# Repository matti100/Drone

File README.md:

# Autonomous Quadrotor Project

A multidisciplinary quadrotor project developed to study and implement the main engineering aspects of a small unmanned aerial vehicle, combining **flight dynamics, simulation, guidance and control, state estimation, electronics, embedded systems, hardware testing and IoT-based control**.

The project combines a MATLAB/Simulink simulation environment with the supporting embedded software, electronics, documentation, testing activities and web interface required for a complete quadrotor system.

---

## Overview

The project was developed to apply aerospace engineering concepts to a real-world autonomous flight system.

The main areas investigated throughout the project are:

* 6-DOF quadrotor flight dynamics
* Nonlinear system modeling
* Linearization and system analysis
* PID control
* Linear Quadratic Regulator (LQR)
* Nonlinear Model Predictive Control (NMPC)
* Kalman-filter-based state estimation
* Sensor fusion
* Trajectory tracking
* Controller tuning
* Embedded systems and Arduino
* Electronics and PCB design
* Hardware testing
* IoT-based drone control

The repository is organized into separate directories according to the different aspects of the project, from theoretical modeling and simulation to embedded implementation and system testing.

---

# Repository Structure

```text
Drone/
│
├── simulator/
│   ├── MATLAB and Simulink simulation files
│   └── Flight dynamics, control and state-estimation models
│
├── arduino_sketches/
│   ├── Main Arduino code
│   ├── Supporting functions
│   └── Required libraries and modules
│
├── electronics/
│   ├── Electrical schematics
│   └── PCB designs
│
├── docs/
│   ├── Project documentation
│   └── Component datasheets
│
├── testing/
│   └── Hardware and system testing
│
├── WebApp/
│   └── drone-web-app/
│       └── Web application for IoT-based drone control
│
└── README.md
```

Each directory addresses a different part of the overall system.

---

# Simulator

The `simulator/` directory contains the **MATLAB and Simulink simulation environment** developed to model, analyze and control the quadrotor before its physical implementation.

The simulator provides a model-based environment in which the vehicle dynamics, control algorithms, state-estimation techniques and trajectory-tracking performance can be developed and evaluated independently of the physical hardware.

The main components investigated within the simulator are:

* Nonlinear quadrotor dynamics
* Linearized hover model
* Stability and controllability analysis
* PID control
* LQR control
* Nonlinear Model Predictive Control
* Kalman-filter-based state estimation
* Controller tuning
* Closed-loop trajectory tracking
* Simulation visualization and animation

---

## Running the Simulator

The main entry point for the simulation is `simulator.m`, located in the `simulator/` directory.

Before running the simulation, open `simulator.m` and configure the vehicle parameters, initial conditions, desired state, simulation settings, controller, state estimator and visualization options.

Once the parameters have been configured, run:

```matlab
simulator
```

The simulation initializes the quadrotor model, executes the selected control and estimation architecture and generates the requested plots and animation.

---

### 1. Vehicle Parameters

The physical parameters of the quadrotor can be modified at the beginning of `simulator.m`.

```matlab
params.m = 0.8;                 % [kg] Mass

params.Ix = 15.67e-3;           % [kg m^2] Moment of inertia about X
params.Iy = 15.67e-3;           % [kg m^2] Moment of inertia about Y
params.Iz = 28.34e-3;           % [kg m^2] Moment of inertia about Z

params.armLength = 0.3;         % [m] Arm length
params.bodySize = 0.2;          % [m] Body size
params.rotRad = 0.1;             % [m] Rotor radius

params.k_f = 1.4e-5 / 9.54929658;  % Lift coefficient
params.k_m = 1.78e-6 / 9.54929658; % Torque coefficient

params.g = 9.81;                % [m/s^2] Gravitational acceleration
```

These parameters define the physical model used by the simulator.

The parameters that can be modified include:

| Parameter          | Description                               | Unit  |
| ------------------ | ----------------------------------------- | ----- |
| `params.m`         | Vehicle mass                              | kg    |
| `params.Ix`        | Principal moment of inertia about X       | kg·m² |
| `params.Iy`        | Principal moment of inertia about Y       | kg·m² |
| `params.Iz`        | Principal moment of inertia about Z       | kg·m² |
| `params.armLength` | Distance from the center to the rotor arm | m     |
| `params.bodySize`  | Approximate body size                     | m     |
| `params.rotRad`    | Rotor radius                              | m     |
| `params.k_f`       | Rotor lift coefficient                    | —     |
| `params.k_m`       | Rotor torque coefficient                  | —     |
| `params.g`         | Gravitational acceleration                | m/s²  |

The inertia matrix is then constructed as:

```matlab
params.I = diag([params.Ix, params.Iy, params.Iz]);
```

---

### 2. Numerical Integration

The simulation integration step is controlled by:

```matlab
params.dt = 0.001;       % [s]
```

The current implementation uses **explicit Euler integration** to propagate the nonlinear equations of motion.

Therefore, `params.dt` controls the numerical integration step and directly affects both the simulation resolution and computational cost.

A smaller value generally provides a finer temporal resolution at the expense of increased computational cost.

---

### 3. Initial Conditions

The initial state of the quadrotor is defined through the 12-state vector:

```matlab
x0 = zeros(12,1);
```

The state follows the convention:

```text
x0 = [x y z vx vy vz phi theta psi p q r]ᵀ
```

Individual initial conditions can be modified directly:

```matlab
x0(1) = 0;       % Initial x position [m]
x0(2) = 0;       % Initial y position [m]
x0(3) = 0;       % Initial z position [m]

x0(4) = 0;       % Initial x velocity [m/s]
x0(5) = 0;       % Initial y velocity [m/s]
x0(6) = 0;       % Initial z velocity [m/s]

x0(7) = 0.3;     % Initial roll [rad]
x0(8) = 0.5;     % Initial pitch [rad]
x0(9) = 0;       % Initial yaw [rad]

x0(10) = 0;      % Initial roll rate [rad/s]
x0(11) = 0;      % Initial pitch rate [rad/s]
x0(12) = 0;      % Initial yaw rate [rad/s]
```

This allows the user to investigate different initial flight conditions and attitude perturbations.

---

### 4. Desired State

The target position and attitude are defined through the `desideredState` structure:

```matlab
desideredState = struct();

desideredState.rDes = [-0.5, 1, 1]';    % [m]
desideredState.attDes = [0, 0, 0]';     % [rad]
```

The desired state consists of:

* Desired position: `rDes = [x, y, z]`
* Desired attitude: `attDes = [phi, theta, psi]`

For example, to command the quadrotor to a different position:

```matlab
desideredState.rDes = [1, 2, 1.5]';
```

The desired yaw angle can also be modified:

```matlab
desideredState.attDes = [0, 0, pi/2]';
```

---

### 5. Simulation Time

The simulation interval is defined using:

```matlab
t0 = 0;          % [s]
tmax = 10;       % [s]

tspan = [t0, tmax];
```

Modify `tmax` to change the total simulation duration.

For example:

```matlab
tmax = 20;
```

runs the simulation for 20 seconds.

---

### 6. Control Mode

The controller is selected using the `control` flag:

```matlab
control = 2;
```

The available modes are:

| Value | Configuration            |
| ----: | ------------------------ |
|  `-1` | PID + linear dynamics    |
|   `0` | PID + nonlinear dynamics |
|   `1` | LQR + linear dynamics    |
|   `2` | LQR + nonlinear dynamics |
|   `3` | Nonlinear MPC            |

For example:

```matlab
control = 0;
```

runs the PID controller using the nonlinear quadrotor dynamics.

To evaluate the LQR controller on the nonlinear plant:

```matlab
control = 2;
```

To use nonlinear MPC:

```matlab
control = 3;
```

The different configurations allow the effect of model linearization and nonlinear dynamics on closed-loop performance to be investigated.

---

### 7. State Estimation

The state-estimation architecture is selected using:

```matlab
estimation = 0;
```

The available options are:

| Value | Configuration       |
| ----: | ------------------- |
|   `0` | No state estimation |
|   `1` | Kalman filter       |

When `estimation = 0`, the controller receives the simulated state directly.

When `estimation = 1`, simulated accelerometer and gyroscope measurements are generated with noise and processed by the Kalman filter before being provided to the control architecture.

For example:

```matlab
estimation = 1;
```

enables the Kalman-filter-based state estimator.

---

### 8. Discrete-Time Sampling

The controller and estimator sampling time is controlled by:

```matlab
sampleTime = 0.005;       % [s]
```

The integration step `params.dt` and the controller/estimator sampling time are independent.

This allows the simulator to represent a system where the continuous-time dynamics are integrated at a finer resolution than the controller and estimator update rate.

Setting:

```matlab
sampleTime = params.dt;
```

makes the controller and estimator update at every integration step.

---

### 9. Visualization

Two flags control the graphical output:

```matlab
plot_flag = 1;
anim_flag = 1;
```

Set:

```matlab
plot_flag = 1;
```

to generate the simulation plots or:

```matlab
plot_flag = 0;
```

to disable plotting.

The animation can similarly be enabled or disabled using:

```matlab
anim_flag = 1;
```

or:

```matlab
anim_flag = 0;
```

When enabled, the simulator generates 2D views of the XY, YZ and XZ planes as well as a 3D visualization of the quadrotor trajectory.

---

### 10. PID Gain Tuning

When using PID control, the controller gains can be manually specified through the `kP`, `kI` and `kD` vectors.

The six controlled quantities correspond to:

```text
1. Altitude
2. Desired roll
3. Desired pitch
4. Roll
5. Pitch
6. Yaw
```

For example:

```matlab
kP = [20;
      -0.4;
       0.4;
       1;
       1;
       1.2];

kI = [10;
      -0.09;
       0.09;
       0.13;
       0.13;
       0.03];

kD = [10;
      -0.25;
       0.25;
       0.66;
       0.66;
       0.9];
```

These values are passed to `gainBuilder()` and then used by the PID controllers.

---

### 11. Automatic PID Tuning

The simulator also provides two automated PID tuning methods through the `tuner_flag`.

```matlab
tuner_flag = 0;
```

The available options are:

| Value | Tuning method       |
| ----: | ------------------- |
|   `0` | No automatic tuning |
|   `1` | Gradient Descent    |
|   `2` | Genetic Algorithm   |

#### Gradient Descent

```matlab
tuner_flag = 1;
```

The current implementation uses:

```matlab
maxIter = 10000;
tol = 1e-6;
alpha = 10;
```

The initial PID gains are randomly generated and then optimized using the PID tuning routine.

The resulting gains are saved to:

```text
tunedGains_gradient.mat
```

#### Genetic Algorithm

```matlab
tuner_flag = 2;
```

The current implementation uses:

```matlab
pop_size = 100;
maxGen = 2000;
tol = 1;
mutation_rate = 0.6;
kMax = 10;
```

The optimized gains are saved to:

```text
tunedGains_ga.mat
```

When automatic tuning is enabled, plotting is automatically disabled during the optimization process to avoid generating unnecessary graphical output.

---

### 12. Nonlinear MPC Parameters

When:

```matlab
control = 3;
```

the nonlinear MPC controller is used.

The main MPC parameters are defined inside the `MPC()` method in `Drone3.m`.

The prediction horizon is:

```matlab
N = 25;
```

and the MPC prediction time step is:

```matlab
dT = 0.1;
```

The control inputs are constrained by:

```text
0 ≤ u₁ ≤ 100
-100 ≤ u₂ ≤ 100
-100 ≤ u₃ ≤ 100
-100 ≤ u₄ ≤ 100
```

The MPC cost function uses weighting matrices for state-tracking error and control effort:

```matlab
Q = eye(6)*10;
Q(3,3) = 100;
Q(6,6) = 50;

R = eye(4)*5;
```

The optimization problem is solved using MATLAB's `fmincon` with the interior-point algorithm.

---

### 13. Running a Basic Simulation

A simple way to run the simulator is to use the default configuration:

```matlab
control = 2;       % LQR + nonlinear dynamics
estimation = 0;    % No state estimation

plot_flag = 1;
anim_flag = 1;

tuner_flag = 0;
```

Then run:

```matlab
simulator
```

The simulator will:

1. Initialize the vehicle parameters.
2. Define the initial and desired states.
3. Select the controller and state-estimation architecture.
4. Initialize the `Drone3` object.
5. Propagate the quadrotor dynamics.
6. Compute the control inputs at the selected sampling rate.
7. Log the system trajectory and control inputs.
8. Generate the requested plots and animation.

---

### 14. Experimenting with Different Configurations

The simulator is designed to make controller and model comparisons straightforward.

For example, the following configurations can be compared:

```matlab
% PID + nonlinear dynamics
control = 0;

% LQR + linear dynamics
control = 1;

% LQR + nonlinear dynamics
control = 2;

% Nonlinear MPC
control = 3;
```

The effect of state estimation can then be investigated independently:

```matlab
% Perfect state information
estimation = 0;

% Kalman-filter-based estimation
estimation = 1;
```

This makes it possible to perform controlled comparisons between different guidance, control and navigation configurations without modifying the underlying quadrotor model.

---

## Quadrotor State Representation

The quadrotor is represented using a 12-state vector:

$$
\mathbf{x} =
\begin{bmatrix}
x & y & z &
v_x & v_y & v_z &
\phi & \theta & \psi &
p & q & r
\end{bmatrix}^T
$$

where:

* $x,y,z$ — inertial position
* $v_x,v_y,v_z$ — inertial velocity
* $\phi,\theta,\psi$ — roll, pitch and yaw angles
* $p,q,r$ — body-frame angular velocities

The model describes the coupled translational and rotational motion of the vehicle.

---

## Nonlinear Dynamics

The simulator implements a nonlinear 6-DOF rigid-body model of the quadrotor.

The dynamics account for:

* Translational motion
* Rotational motion
* Gravity
* Rotor-generated thrust
* Control torques
* Attitude kinematics
* Coupling between translational and rotational dynamics

The rotor inputs are converted into the corresponding total thrust and body moments acting on the vehicle.

The resulting nonlinear equations of motion are numerically integrated during the simulation to obtain the time evolution of the vehicle state.

---

## Linearization

To enable linear control design, the nonlinear model is linearized around a **hover equilibrium condition**.

The resulting model is expressed in state-space form:

$$
\dot{\mathbf{x}} = A\mathbf{x} + B\mathbf{u}
$$

where:

* $A$ is the state matrix
* $B$ is the input matrix
* $\mathbf{x}$ is the vehicle state
* $\mathbf{u}$ represents the control inputs

The linearized model provides the basis for system analysis and LQR controller design.

---

## System Analysis

The simulator includes analysis of the linearized system before controller design.

### Stability Analysis

The eigenvalues of the state matrix are evaluated to investigate the stability characteristics of the linearized system.

### Controllability Analysis

The controllability matrix is computed to verify whether the system states can be controlled through the available inputs.

These analyses provide the theoretical basis for the subsequent controller design.

---

# Control Architectures

Several control strategies are implemented to evaluate different approaches to quadrotor flight control.

The simulator allows controllers to be tested using both the **linearized** and **nonlinear** plant models where applicable.

---

## PID Control

A PID-based controller is implemented for the main flight-control variables, including:

* Altitude
* Roll
* Pitch
* Yaw

The controller provides a relatively simple baseline for evaluating closed-loop flight performance.

The implementation includes numerical integration and differentiation of the tracking error for the integral and derivative terms.

---

## Linear Quadratic Regulator

An LQR controller is designed using the linearized hover model.

The controller minimizes a quadratic cost function:

$$
J =
\int_0^\infty
\left(
\mathbf{x}^T Q \mathbf{x}
+
\mathbf{u}^T R \mathbf{u}
\right)dt
$$

where:

* $Q$ weights deviations of the system states
* $R$ penalizes control effort

The weighting matrices can be modified to investigate the trade-off between tracking performance and control effort.

The LQR controller can be evaluated both on the linearized model and on the nonlinear quadrotor dynamics.

---

## Nonlinear Model Predictive Control

A nonlinear Model Predictive Controller is also implemented.

At each control step, the controller predicts the future evolution of the nonlinear quadrotor over a finite prediction horizon and solves an optimization problem to determine the control inputs.

The implemented formulation accounts for:

* Position tracking error
* Attitude tracking error
* Control effort

The prediction horizon used in the implementation is:

$$
N = 25
$$

This provides a framework for comparing nonlinear predictive control with conventional PID and LQR approaches.

---

# State Estimation

The simulator includes a **Kalman-filter-based state-estimation framework**.

The estimator uses simulated measurements from:

* Accelerometers
* Gyroscopes

to estimate the vehicle state in the presence of measurement noise.

The estimation process follows a prediction/correction structure:

### Prediction

The current state estimate is propagated using the system dynamics.

### Correction

The predicted state is corrected using the available sensor measurements.

The implementation uses the relevant system and measurement Jacobians required by the nonlinear estimation framework.

The estimated state can then be used by the controller, allowing the effect of imperfect state information on closed-loop performance to be investigated.

---

# Controller Tuning

The simulator includes automated controller-tuning capabilities.

Two optimization approaches are available:

### Gradient Descent

Gradient-based optimization can be used to iteratively adjust controller parameters according to the selected performance objective.

### Genetic Algorithm

A genetic-algorithm-based approach is also available for controller parameter optimization.

These methods provide an alternative to manually selecting controller gains.

---

# Simulation Configurations

The simulation framework allows different combinations of plant models, controllers and state-estimation configurations to be evaluated.

### Plant Model

```text
Plant Model
├── Linear dynamics
└── Nonlinear dynamics
```

### Controller

```text
Controller
├── PID
├── LQR
└── Nonlinear MPC
```

### State Estimation

```text
State Estimation
├── No estimation
└── Kalman filter
```

The simulator can therefore be used to investigate questions such as:

* How does a controller designed from a linearized model perform on the nonlinear plant?
* How do nonlinearities affect closed-loop trajectory tracking?
* How does state estimation influence controller performance?
* How do PID, LQR and nonlinear MPC compare?
* How does controller tuning affect the resulting response?

---

# Visualization

The simulator provides visualization tools for analyzing the resulting flight behavior.

The available outputs include:

* Position and trajectory evolution
* Vehicle attitude
* Control inputs
* Estimated trajectory
* 2D trajectory visualization
* 3D trajectory visualization
* Flight animation

These tools allow the closed-loop response of the vehicle to be inspected and different control architectures to be compared.

---

# Other Repository Components

## `arduino_sketches/`

The `arduino_sketches/` directory contains the **embedded software** developed for the physical quadrotor.

It includes the main Arduino code together with supporting functions, libraries and modules required by the onboard system.

This part of the project connects the mathematical and simulation environment with the constraints of a real embedded implementation.

---

## `electronics/`

The `electronics/` directory contains the hardware design associated with the quadrotor.

It includes:

* Electrical schematics
* PCB designs

This section documents the electronic architecture used to support the physical implementation of the vehicle.

---

## `docs/`

The `docs/` directory contains the technical documentation developed throughout the project together with the datasheets of the components used in the system.

The documentation provides the theoretical and engineering background behind the design and implementation choices made throughout the project.

---

## `testing/`

The `testing/` directory contains material related to the **testing and validation of the physical system**.

Testing provides the connection between the simulated models and the real-world implementation, allowing the behavior of the developed hardware and software to be evaluated.

---

## `WebApp/drone-web-app/`

The `WebApp/drone-web-app/` directory contains the **web application developed as an IoT interface for the drone**.

The application provides a higher-level interface through which the user can interact with the quadrotor system.

---

# Project Workflow

The overall development process can be summarized as:

```text
                 THEORETICAL MODEL
                        │
                        ▼
               Nonlinear Dynamics
                        │
                        ▼
                  Linearization
                        │
              ┌─────────┴─────────┐
              ▼                   ▼
       System Analysis      Controller Design
       • Stability          • PID
       • Controllability    • LQR
                            • NMPC
              │                   │
              └─────────┬─────────┘
                        ▼
                 State Estimation
                 • Kalman Filter
                        │
                        ▼
                  MATLAB/Simulink
                     Simulation
                        │
                        ▼
               Embedded Implementation
                        │
              ┌─────────┴─────────┐
              ▼                   ▼
          Electronics           Arduino
              │                   │
              └─────────┬─────────┘
                        ▼
                  Physical Drone
                        │
                        ▼
                     Testing
                        │
                        ▼
                 IoT Web Interface
```

The workflow connects the different components of the project, from mathematical modeling and simulation to embedded implementation, hardware testing and user interaction.

---

# Technologies

### Simulation & Control

* MATLAB
* Simulink
* Nonlinear dynamics
* PID
* LQR
* Nonlinear MPC
* Kalman filtering
* Numerical optimization
* Monte Carlo methods

### Embedded Systems

* Arduino
* Embedded C/C++
* Sensors

### Electronics

* Electrical schematics
* PCB design

### Software & IoT

* Web application
* IoT-based drone control

---

# Project Goals

The main goals of the project are to:

1. Develop a mathematical model of a quadrotor.
2. Analyze its nonlinear 6-DOF flight dynamics.
3. Linearize the system around hover and analyze its properties.
4. Develop and compare different control architectures.
5. Investigate state estimation and sensor fusion.
6. Optimize controller parameters.
7. Implement the developed concepts on embedded hardware.
8. Design and document the supporting electronics.
9. Test and validate the physical system.
10. Develop an IoT-based interface for interaction with the drone.

The project is intended as a complete engineering workflow connecting **aerospace dynamics, control, simulation, estimation, embedded systems, electronics and hardware implementation**.

---

# Author

**Matteo Colussi**

M.S. Aerospace Engineering
Georgia Institute of Technology

B.S. Aerospace Engineering
Politecnico di Milano

---

# License

This project is intended for educational and research purposes.

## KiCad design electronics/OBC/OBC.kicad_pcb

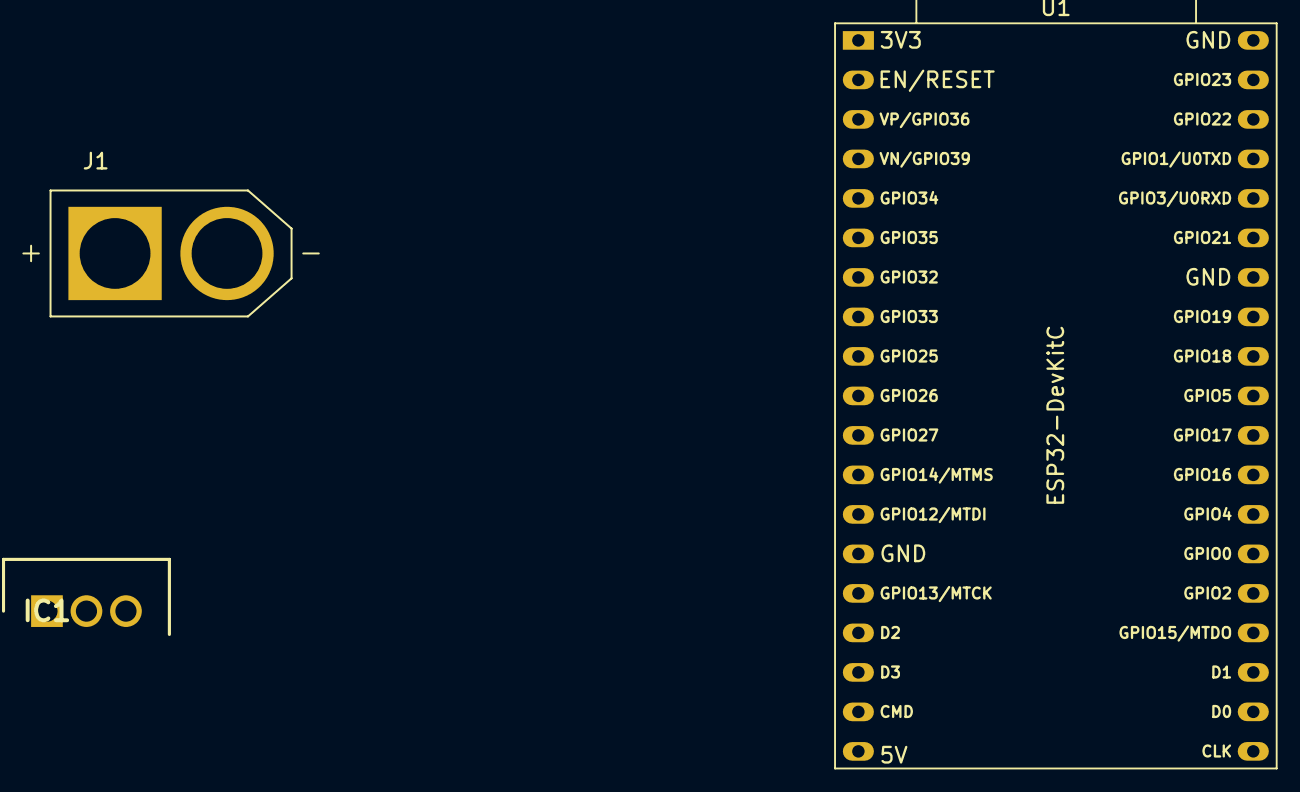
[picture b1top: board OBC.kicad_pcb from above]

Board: 2 copper layers, 3 parts (0 on the bottom side), 4 nets, no tracks yet.

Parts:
IC1: MIC29300-3.3WT; TO254P483X1022X1603-3P
J1: XT60-M; AMASS_XT60-M
U1: ESP32-DevKitC

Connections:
+BATT: IC1.1 (IN), J1.P (POS)
-BATT: IC1.2 (GND), J1.N (NEG)
EXT_5V: IC1.3 (OUT), U1.19 (5V)
GND: U1.14 (GND), U1.32 (GND), U1.38 (GND)

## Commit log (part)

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2024-04-28 upload arduino sketches
2024-04-28 change directory tree
2024-10-01 update repo
2024-10-01 folder organization
2024-10-01 token github
2024-10-01 change position of token_github
2024-10-01 Arduino Test code
2024-10-02 Tuning GA
2024-10-03 pid tuner changes
2024-10-07 motors library
2024-10-07 TMTC library
2024-10-07 webApp
2024-10-08 server
2024-10-08 webapp updates
2024-10-09 webapp update
2024-10-10 TMTC updates
2024-10-11 linearization options for simulator
2024-10-11 update OBSW motor velocity
2024-10-11 motor library updates
2024-10-11 manual tuning
2025-05-12 directory changes
2025-05-12 small changes
2025-05-12 Drone changes
2025-05-12 new branch
2025-05-12 ga tuner updates
2025-05-12 control improvement
2025-05-12 Simulator update
2025-05-12 simulink
2025-05-12 control logic update
2025-05-12 pid controller done
2025-05-12 filter arduino
2025-05-12 dynamics function handle
2025-05-12 arduino changes
2025-05-12 workspace1
2025-05-12 cleaning simulator
2025-05-12 matlab Drive
2025-05-12 kalman filter script
2025-05-12 small changes to simulink
2025-05-12 simulink + estimator
2025-05-12 ekf script
2025-05-12 sampleTime + simulink
2025-05-12 general commit

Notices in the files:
README.md:
License:
This project is intended for educational and research purposes.
